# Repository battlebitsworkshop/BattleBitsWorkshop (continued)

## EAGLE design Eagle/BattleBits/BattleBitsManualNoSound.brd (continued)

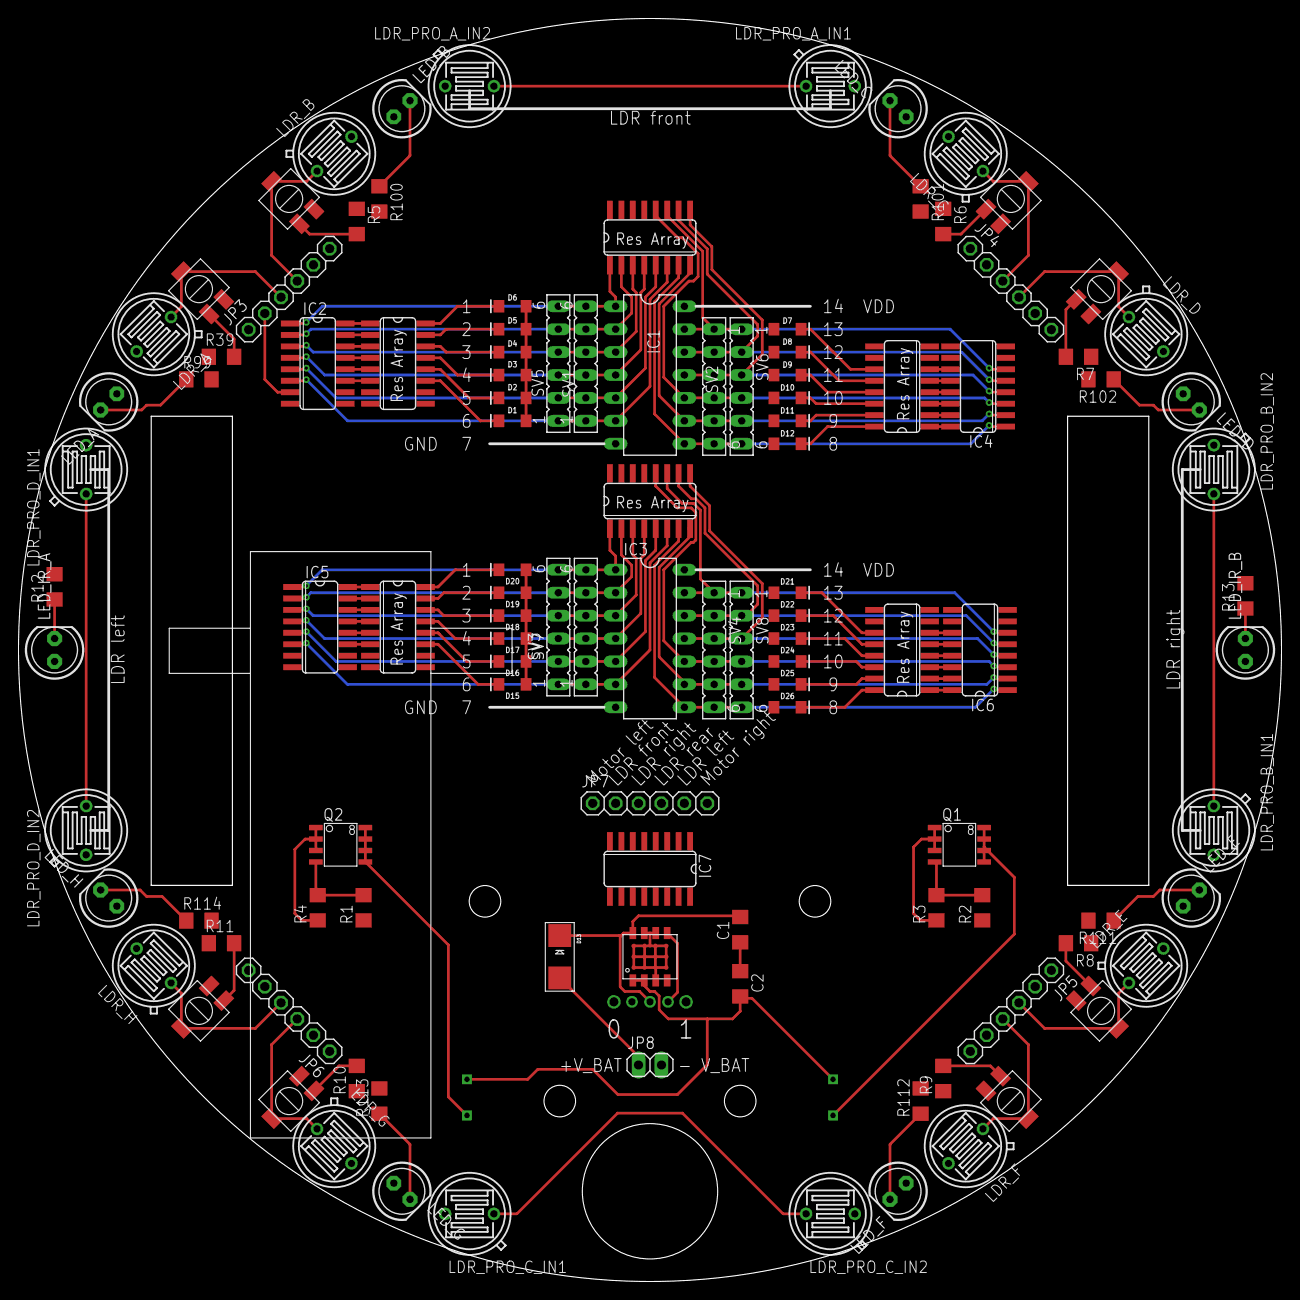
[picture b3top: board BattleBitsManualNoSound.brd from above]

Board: 2 copper layers, 140.0 x 140.0 mm, 116 parts (1 on the bottom side), 129 nets.

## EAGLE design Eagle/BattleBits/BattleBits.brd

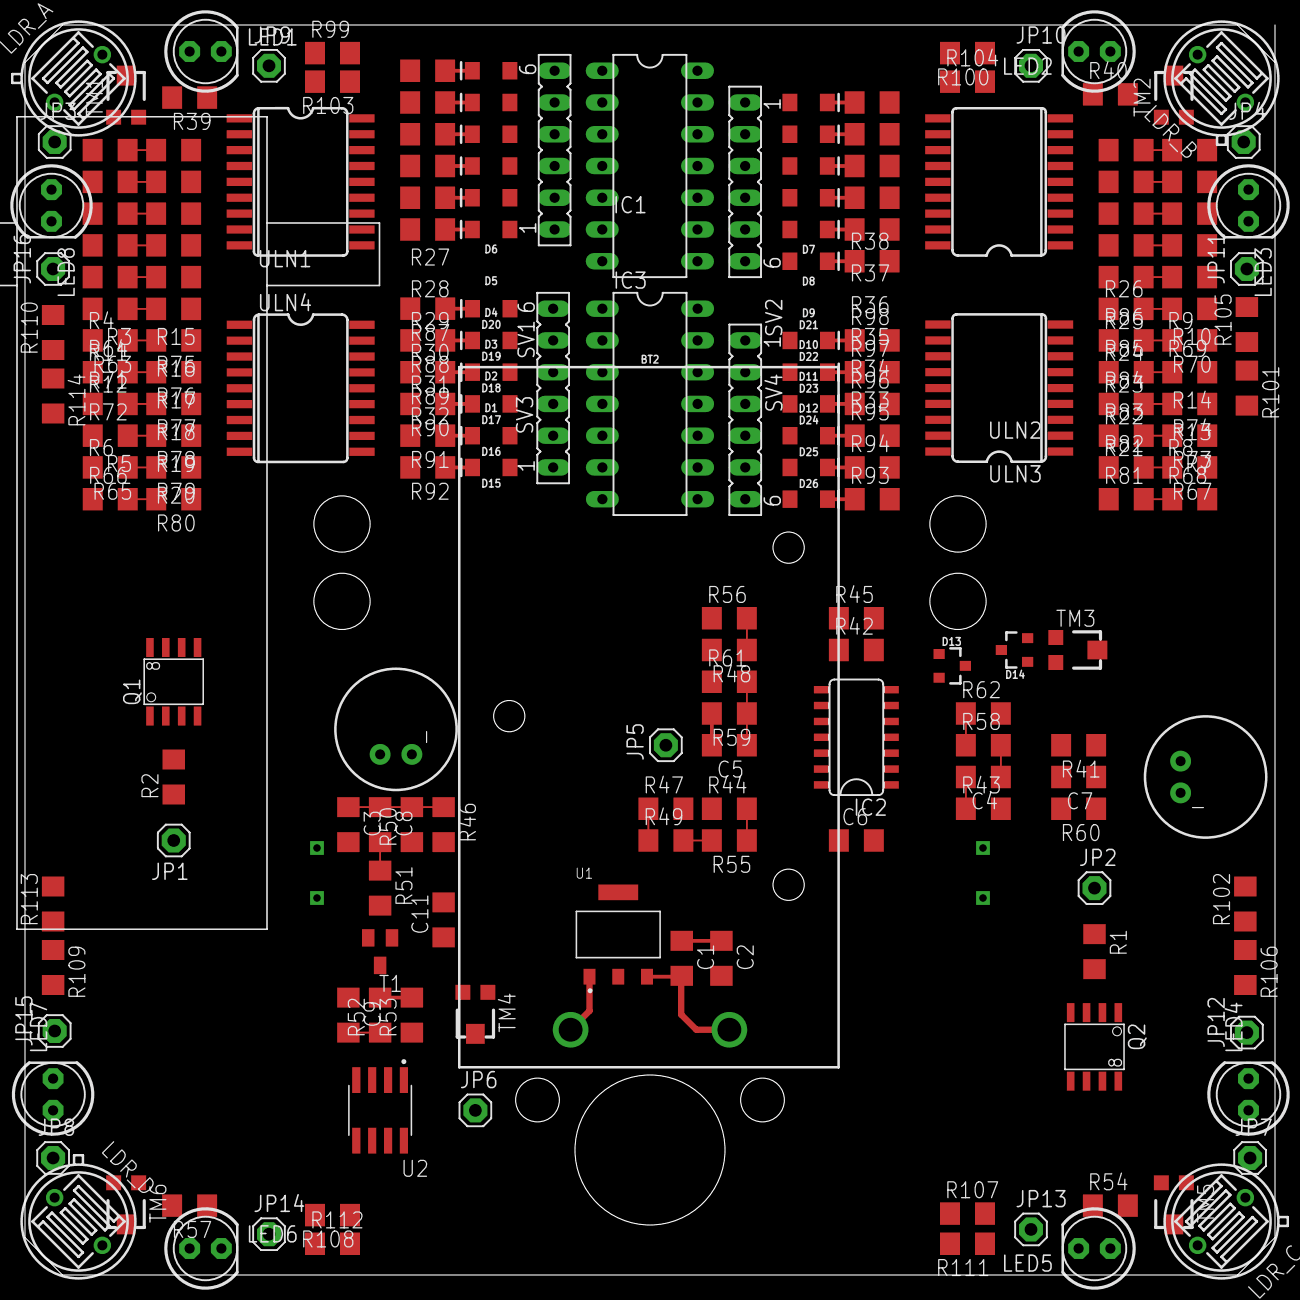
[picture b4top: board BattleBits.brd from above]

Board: 2 copper layers, 100.0 x 100.0 mm, 205 parts (1 on the bottom side), 167 nets.

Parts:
BT2: BATTCON_9V
C1, C2, C5, C7: 10uF; C3216
C3, C6, C8, C9: 0.1uF; C3216
C4, C11: 1.0uF; C3216
D1, D2, D3, D4, D5, D6, D7, D8, D9, D10, D11, D12, D15, D16, D17, D18, D19, D20, D21, D22, D23, D24, D25, D26: LED-1206
D13, D14: 40V, 120 mA; SOT23-3
IC1, IC3: 4001N; DIL14
IC2: LMV324; SO014
JP1, JP2, JP3, JP4, JP5, JP6, JP7, JP8, JP9, JP10, JP11, JP12, JP13, JP14, JP15, JP16: 1X01
LDR_A: V1060_21; TO-5_V10
LDR_B: V1060_21; TO-5_V10
LDR_C: V1060_21; TO-5_V10
LDR_D: V1060_21; TO-5_V10
LED1, LED2, LED3, LED4, LED5, LED6, LED7, LED8: LED5MM
MIC1, MIC2: MIC9.7MM; MIC-9.7MM
Q1, Q2: FDS5680; SO-8
R1, R2, R3, R4, R5, R6, R7, R8, R9, R10, R11, R12, R13, R14, R15, R16, R17, R18, R19, R20, R21, R22, R23, R24, R25, R26, R27, R28, R29, R30, R31, R32, R33, R34, R35, R36, R37, R38, R42, R43, R45, R46, R52, R53, R58, R59, R63, R64, R65, R66, R67, R68, R69, R70, R71, R72, R73, R74, R75, R76, R77, R78, R79, R80, R81, R82, R83, R84, R85, R86, R87, R88, R89, R90, R91, R92, R93, R94, R95, R96, R97, R98, R103, R104, R105, R106, R107, R108, R109, R110: 10K, 1%; R3216
R39, R40, R54, R57: 2K, 1%; R3216
R41, R44, R55: 1K, 1%; R3216
R47, R61, R99, R100, R101, R102, R111, R112, R113, R114: 100, 1%; R3216
R48, R49: 100K, 1%; R3216
R50: 51K, 1%; R3216
R51: 510K, 1%; R3216
R56: 3.3K, 1%; R3216
R60: 2.2K, 1%; R3216
R62: 22K, 1%; R3216
SV1, SV2, SV3, SV4: FE06
T1: SOT23-BEC
TM1, TM2, TM5, TM6: 100K trimpot; TC33X
TM3: 1M trimpot; TC33X
TM4: 10k trimpot; TC33X
U1: NCP1117_5V; SOT-223
U2: LM293D; 8-SOIC
U$1, U$2: MOTOR; GEARMOTOR
ULN1, ULN2, ULN3, ULN4: SO18L

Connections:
40XX_CH_A_IN_A: IC1.1, R3.1, R15.2, SV1.6
40XX_CH_A_IN_B: IC1.2, R4.2, R16.2, SV1.5
40XX_CH_A_OUT: IC1.3, R11.2, R17.2, SV1.4
40XX_CH_B_IN_A: IC1.5, R5.1, R19.2, SV1.2
40XX_CH_B_IN_B: IC1.6, R6.2, R20.2, SV1.1
40XX_CH_B_OUT: IC1.4, R12.2, R18.2, SV1.3
40XX_CH_C_IN_A: IC1.8, R8.1, R21.2, SV2.6
40XX_CH_C_IN_B: IC1.9, R7.2, R22.2, SV2.5
40XX_CH_C_OUT: IC1.10, R13.2, R23.2, SV2.4
40XX_CH_D_IN_A: IC1.12, R9.1, R25.2, SV2.2
40XX_CH_D_IN_B: IC1.13, R10.2, R26.2, SV2.1
40XX_CH_D_OUT: IC1.11, R14.2, R24.2, SV2.3
40XX_CH_E_IN_A: IC3.1, R63.1, R75.2, SV3.6
40XX_CH_E_IN_B: IC3.2, R64.2, R76.2, SV3.5
40XX_CH_E_OUT: IC3.3, R71.2, R77.2, SV3.4
40XX_CH_F_IN_A: IC3.5, R65.1, R79.2, SV3.2
40XX_CH_F_IN_B: IC3.6, R66.2, R80.2, SV3.1
40XX_CH_F_OUT: IC3.4, R72.2, R78.2, SV3.3
40XX_CH_G_IN_A: IC3.8, R68.1, R81.2, SV4.6
40XX_CH_G_IN_B: IC3.9, R67.2, R82.2, SV4.5
40XX_CH_G_OUT: IC3.10, R73.2, R83.2, SV4.4
40XX_CH_H_IN_A: IC3.12, R69.1, R85.2, SV4.2
40XX_CH_H_IN_B: IC3.13, R70.2, R86.2, SV4.1
40XX_CH_H_OUT: IC3.11, R74.2, R84.2, SV4.3
AMPENV: IC2.14, R44.2, R55.1
GND: BT2.-, C1.1, C2.1, C3.2, C5.2, C6.2, C9.1, C11.2, IC1.7, IC2.5, IC2.11, IC3.7, LDR_A.1, LDR_B.1, LDR_C.1, LDR_D.1, MIC1.2, MIC2.2, Q1.1, Q1.2, Q1.3, Q2.1, Q2.2, Q2.3, R3.2, R4.1, R5.2, R6.1, R7.1, R8.2, R9.2, R10.1, R11.1, R12.1, R13.1, R14.1, R45.1, R50.1, R56.1, R59.2, R63.2, R64.1, R65.2, R66.1, R67.1, R68.2, R69.2, R70.1, R71.1, R72.1, R73.1, R74.1, T1.E, TM4.1, U1.1, U2.4, ULN1.9, ULN2.9, ULN3.9, ULN4.9
LED_CH_A_IN: JP9.1, R103.2
LED_CH_A_OUT: R99.2, ULN1.12
LED_CH_B_IN: JP10.1, R104.2
LED_CH_B_OUT: R100.2, ULN1.11
LED_CH_C_IN: JP11.1, R105.2
LED_CH_C_OUT: R101.2, ULN2.12
LED_CH_D_IN: JP12.1, R106.2
LED_CH_D_OUT: R102.2, ULN2.11
LED_CH_E_IN: JP13.1, R107.2
LED_CH_E_OUT: R111.2, ULN4.12
LED_CH_F_IN: JP14.1, R108.2
LED_CH_F_OUT: R112.2, ULN4.11
LED_CH_G_IN: JP15.1, R109.2
LED_CH_G_OUT: R113.2, ULN3.12
LED_CH_H_IN: JP16.1, R110.2
LED_CH_H_OUT: R114.2, ULN3.11
LIGHT_SENSOR_A_OUT: JP3.1, LDR_A.2, TM1.3
LIGHT_SENSOR_B_OUT: JP4.1, LDR_B.2, TM2.3
LIGHT_SENSOR_C_OUT: JP7.1, LDR_C.2, TM5.3
LIGHT_SENSOR_D_OUT: JP8.1, LDR_D.2, TM6.3
MOTOR_A-: Q1.5, Q1.6, Q1.7, Q1.8, U$1.P$1
MOTOR_B-: Q2.5, Q2.6, Q2.7, Q2.8, U$2.P$1
N$: C4.2, IC2.1, R43.1
unnamed: R15.1, ULN1.1
unnamed: Q1.4, R2.2
unnamed: Q2.4, R1.2
unnamed: R16.1, ULN1.2
unnamed: R17.1, ULN1.3
unnamed: R18.1, ULN1.4
unnamed: R19.1, ULN1.5
unnamed: R20.1, ULN1.6
unnamed: R21.1, ULN2.1
unnamed: R22.1, ULN2.2
unnamed: R23.1, ULN2.3
unnamed: R24.1, ULN2.4
unnamed: R25.1, ULN2.5
unnamed: R26.1, ULN2.6
unnamed: R27.2, ULN1.18
unnamed: D6.C, R27.1
unnamed: R28.2, ULN1.17
unnamed: D5.C, R28.1
unnamed: R29.2, ULN1.16
unnamed: D4.C, R29.1
unnamed: R30.2, ULN1.15
unnamed: D3.C, R30.1
unnamed: R31.2, ULN1.14
unnamed: D2.C, R31.1
unnamed: R32.2, ULN1.13
unnamed: D1.C, R32.1
unnamed: D12.C, R33.1
unnamed: D11.C, R34.1
unnamed: D10.C, R35.1
unnamed: D9.C, R36.1
unnamed: D8.C, R37.1
unnamed: D7.C, R38.1
unnamed: R33.2, ULN2.18
unnamed: R34.2, ULN2.17
unnamed: R35.2, ULN2.16
unnamed: R36.2, ULN2.15
unnamed: R37.2, ULN2.14
unnamed: R38.2, ULN2.13
unnamed: R39.2, TM1.2
unnamed: R40.2, TM2.2
unnamed: C7.2, MIC1.1, R60.2
unnamed: IC2.3, R42.2, R45.2
unnamed: IC2.2, R41.2, TM3.2
unnamed: C7.1, R41.1
unnamed: C4.1, R58.2
unnamed: D13.1, IC2.6, R58.1, R62.1
unnamed: D14.1, IC2.7
unnamed: D13.3, D14.3, R61.1, R62.2
unnamed: C5.1, IC2.12, R59.1, R61.2
unnamed: IC2.13, R44.1
unnamed: IC2.9, R48.1, R56.2
unnamed: IC2.10, R49.2, R55.2
unnamed: IC2.8, R47.1, R49.1
unnamed: R43.2, TM3.3
unnamed: C3.1, C8.1, MIC2.1, R46.1, R50.2
unnamed: C8.2, R51.1, T1.B
unnamed: C9.2, R52.1, T1.C, U2.3
unnamed: TM4.2, U2.2
unnamed: JP6.1, R53.1, U2.1
unnamed: JP1.1, R2.1
unnamed: JP2.1, R1.1
unnamed: JP5.1, R47.2
unnamed: R54.2, TM5.2
unnamed: R57.2, TM6.2
unnamed: R75.1, ULN4.1
unnamed: R76.1, ULN4.2
unnamed: R77.1, ULN4.3
unnamed: R78.1, ULN4.4
unnamed: R79.1, ULN4.5
unnamed: R80.1, ULN4.6
unnamed: R81.1, ULN3.1
unnamed: R82.1, ULN3.2
unnamed: R83.1, ULN3.3
unnamed: R84.1, ULN3.4
unnamed: R85.1, ULN3.5
unnamed: R86.1, ULN3.6
unnamed: R87.2, ULN4.18
unnamed: D20.C, R87.1
unnamed: R88.2, ULN4.17
unnamed: D19.C, R88.1
unnamed: R89.2, ULN4.16
unnamed: D18.C, R89.1
unnamed: R90.2, ULN4.15
unnamed: D17.C, R90.1
unnamed: R91.2, ULN4.14
unnamed: D16.C, R91.1
unnamed: R92.2, ULN4.13
unnamed: D15.C, R92.1
unnamed: D26.C, R93.1
unnamed: D25.C, R94.1
unnamed: D24.C, R95.1
unnamed: D23.C, R96.1
unnamed: D22.C, R97.1
unnamed: D21.C, R98.1
unnamed: R93.2, ULN3.18
unnamed: R94.2, ULN3.17
unnamed: R95.2, ULN3.16
unnamed: R96.2, ULN3.15
unnamed: R97.2, ULN3.14
unnamed: R98.2, ULN3.13
unnamed: LED1.K, R99.1
unnamed: LED2.K, R100.1
unnamed: LED3.K, R101.1
unnamed: LED4.K, R102.1
unnamed: R103.1, ULN1.7
unnamed: R104.1, ULN1.8
unnamed: R105.1, ULN2.7
unnamed: R106.1, ULN2.8
unnamed: R107.1, ULN4.7
unnamed: R108.1, ULN4.8
unnamed: R109.1, ULN3.7
unnamed: R110.1, ULN3.8
unnamed: LED5.K, R111.1
unnamed: LED6.K, R112.1
unnamed: LED7.K, R113.1
unnamed: LED8.K, R114.1
VBAT: BT2.+, C1.2, U1.3
VDD: C2.2, C6.1, C11.1, D1.A, D2.A, D3.A, D4.A, D5.A, D6.A, D7.A, D8.A, D9.A, D10.A, D11.A, D12.A, D15.A, D16.A, D17.A, D18.A, D19.A, D20.A, D21.A, D22.A, D23.A, D24.A, D25.A, D26.A, IC1.14, IC2.4, IC3.14, LED1.A, LED2.A, LED3.A, LED4.A, LED5.A, LED6.A, LED7.A, LED8.A, R39.1, R40.1, R42.1, R46.2, R48.2, R51.2, R52.2, R53.2, R54.1, R57.1, R60.1, TM4.3, U1.2, U1.4, U2.8, U$1.P$2, U$2.P$2, ULN1.10, ULN2.10, ULN3.10, ULN4.10

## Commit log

2021-09-02 added dxf
2022-09-05 eagle added
2022-09-05 kicad
2022-09-06 silkscreen added
2022-09-07 gerber
2022-09-27 added sticker
